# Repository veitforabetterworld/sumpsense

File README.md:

# SumpSense

Kapazitive Füllstandssensoren für **14,5-mm-Rohr** (schmaler Stab, 5-mm-Raster). Inspiriert vom [Seeed Grove Water Level Sensor](https://wiki.seeedstudio.com/Grove-Water-Level-Sensor/).

| Platine | Stufen | Bus | Doku |
|---------|--------|-----|------|
| [SumpSense-24i](hardware/sumpsense-24i/README.md) | 24 | I²C | Bestellen → [`firmware`](firmware/README.md#sumpsense-24i) |
| [SumpSense-16z](hardware/sumpsense-16z/README.md) | 16 | Zigbee 3.0 + Ventil | Bestellen → [`firmware`](firmware/README.md#sumpsense-16z) |
| [SumpSense-16z-v2](hardware/sumpsense-16z-v2/README.md) | 16 | Zigbee 3.0 + Ventil, ESP32-H2-MINI-1, 100,0 mm (+ 5,4 mm Antenne) | Bestellen → [`firmware`](firmware/README.md#sumpsense-16z) (`SS_BOARD=2`) |

Gerber/BOM je Board: `hardware/<name>/jlcpcb/` — erzeugen mit `python3 hardware/jlcpcb.py <name>`.

## Boardprüfung

`python3 hardware/check_boards.py [<name>]` führt DRC (mit Schaltplan-Parität) und ERC aus und meldet jeden Fehler und jede Warnung. Erlaubte Ausnahmen stehen in den Projektdateien, damit KiCad und das Skript dasselbe melden:

- `<name>.kicad_dru`: Der Schraubenkopf MH1 darf die Courtyards anderer Bauteile überdecken (einzige Ausnahme).
- `sumpsense-24i.kicad_pro`: In der ERC-Pin-Matrix ist „Bidirektional ↔ Power-Ausgang“ erlaubt, weil PA3 als Adressmerkmal fest an GND/VCC liegt.

Angepasste Footprints liegen in den Projektbibliotheken (`zig:`, `ssi:`), damit es keine Abweichungen von der KiCad-Bibliothek gibt.

Der Git-Hook `.githooks/pre-commit` startet die Prüfung bei jedem Commit, der Platinendateien enthält, und bricht den Commit bei Befunden ab. Einmal pro Klon aktivieren:

```bash
git config core.hooksPath .githooks
```

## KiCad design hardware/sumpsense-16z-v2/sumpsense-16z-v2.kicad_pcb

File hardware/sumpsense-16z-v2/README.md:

# SumpSense-16z-v2

Wie [SumpSense-16z](../sumpsense-16z/README.md), aber mit dem Modul **ESP32-H2-MINI-1-H4S** statt nacktem Chip: Quarz und Antenne sitzen im Modul, Quarz, Leiterantenne und Anpassnetz entfallen. Platine **14 × 100,0 mm**, die Modulantenne steht **5,4 mm** über (gesamt 105,4 mm; v1: 125 mm). Rohr **14,5 mm**, 16 Stufen à **5 mm**, Ausgang für **5-V-Magnetventil**.

## v1 oder v2?

| | v1 (`sumpsense-16z`) | v2 (`sumpsense-16z-v2`) |
|---|---|---|
| Funk | ESP32-H2FH4 + 32-MHz-Quarz + Leiterantenne DN007 | ESP32-H2-MINI-1-H4S (Quarz, Antenne, Funkzulassung im Modul) |
| Länge | 125 mm | 100,0 mm Platine + 5,4 mm Antenne = 105,4 mm |
| Bauhöhe Kopf | ca. 1,2 mm | **2,4 mm** (Modul) |
| LCSC-Lage | Chip „nicht für neue Designs“, Restbestand | Modul neu, Bestand schwankt |
| Teilepreis Funk (1 Stk.) | ≈ 2,19 $ | ≈ 3,77 $ |

Beide Platinen bleiben gepflegt: v1 fertigen, wenn das Modul nicht lieferbar ist.

## Platine bestellen (JLCPCB)

1. [`jlcpcb/`](jlcpcb/): Gerber-ZIP, BOM, CPL. Neu generieren: `python3 ../jlcpcb.py sumpsense-16z-v2`
2. **PCBA einseitig (oben):** Gerber, BOM und CPL hochladen. Die Lötpads auf der Unterseite (J1, J3, JP1) werden nicht bestückt.
3. **Antenne steht über die Platine:** So empfehlen es Espressif und JLCPCB selbst für Module mit Leiterantenne. JLCPCB bestückt nur mit Nutzenrand; der Rand darf nur an den Längsseiten liegen, am Antennenende muss frei bleiben. In der Bestellung als Bemerkung angeben: *„ESP32 module antenna overhangs the board edge on purpose, edge rails on the long sides only“*.
4. In der Bestückungsvorschau prüfen, dass die **Antenne des Moduls über das Platinenende** zeigt (CPL-Drehung des Moduls ist nicht gegen eine echte Bestellung geprüft).

## Anschluss

| Wo | Funktion |
|----|----------|
Alle Anschlüsse sind Lötpads (1,1 × 2,2 mm, Raster 1,425 mm) auf der **Unterseite unter dem Modul**:

| Wo | Pads | Funktion |
|----|------|----------|
| Unterkante | **PAIR** (JP1), **GND**, **5V**, **VLV** (J1) | Versorgung; Magnetventil zwischen **5V** und **VLV**. PAIR = GPIO9, mit dem GND-Pad daneben brücken: Pairing, Werksreset, Download-Modus |
| Oberkante | **D−**, **D+** (J3) | USB nur zum Flashen, dazu GND und 5V von der Unterkante |

Drähte von den Pads weg nach hinten oder zur Seite führen, nicht unter der überstehenden Antenne entlang.

## Aufbau

- **Modul am Platinenende**, nur der Antennenteil (5,4 mm) steht über; die Platinenkante liegt auf der Antennengrenze, 0,3 mm vor den äußeren GND-Pads.
- **Vias unter dem Modul:** Seitenpins und Endreihe gehen direkt unter dem Modul auf die Unterseite. Dadurch beginnen die Bauteile direkt hinter dem Modul.
- **Bauteile hinter dem Modul, dicht gepackt:** Pull-ups R18/R17 und C6 in einer Spalte am Modul, C3 und C4 untereinander daneben, rechts Regler U2, Freilaufdiode D1 senkrecht, R23 und Ventiltreiber Q1; R19 quer unter C4.
- **Alle 16 Sense-Leitungen auf der Unterseite**, kreuzungsfrei; vor der Widerstandsbank gehen sie über Vias nach oben.
- **Widerstandsbank direkt vor MAX:** Die MAX-Linie liegt gleich hinter der Bank in der Lücke vor E1; der Fächer zu den Elektroden knickt direkt hinter der Bank ab und reicht über MAX hinaus. Der Schraubenkopf MH1 (Ø 6 mm) ragt etwa 0,5 mm über die MAX-Linie.
- **GND-Fläche auf Ober- und Unterseite**, freie Flächen im Kopf über GND-Vias verbunden.
- **Vias 0,45/0,2 mm** (JLCPCB-Standard ohne Aufpreis).
- **Bahnbreiten:** Sense 0,2 mm, 3V3 0,3 mm (0,4 mm auf der Unterseite), GND 0,2–0,4 mm je nach Platz, 5V und Ventil 0,5 mm, Elektroden 0,25 mm.
- **Bestückungsdruck nur auf der Unterseite:** MAX-Linie, Eintauchtiefen (in den Lücken vor den Elektroden), Padbeschriftung und Platinenname. Die Gerber-Daten enthalten keinen Druck für die Oberseite (`../jlcpcb.py`).
- **GPIO-Zuordnung** folgt der Modul-Pinreihe (E01…E16 = GPIO 10, 11, 8, 9, 22, 25, 23, 24, 5, 4, 12, 14, 13, 1, 3, 2). Die Firmware braucht dafür `SS_BOARD=2`.
- **EN** mit 10 kΩ / 1 µF (R19, C6) nach Datenblatt; **VBAT** bleibt offen (im Modul an 3V3).
- Pull-ups **R17/R18 (1 MΩ)** an GPIO8/9 wie bei v1 (Messverfahren und Strapping).
- Der Schaltplan wird mit `python3 gen_sch.py` aus der Platine erzeugt.

## Firmware, Pairing, Smart Home

**[Firmware-README](../../firmware/README.md#sumpsense-16z)**: Bauen mit `SS_BOARD=2`, Flashen, PAIR-Tabelle, Home Assistant. Zigbee-Modell und Zigbee2MQTT-Konverter sind dieselben wie bei v1; OTA-Images haben einen eigenen Image-Typ (0x1012), damit v1- und v2-Images nicht vertauscht werden.

## Ungeprüft

- Kein Musteraufbau: Antennenleistung im Rohr, Kapazitätsmessung und Einschaltverhalten (EN-RC) sind nur nach Datenblatt ausgelegt.
- Überstehende Antenne bei JLCPCB nicht mit einer echten Bestellung geprüft (Nutzenrand siehe oben).
- Das Landmuster des Moduls ist nach Espressifs KiCad-Bibliothek nachgebaut; das 3D-Modell ist vereinfacht.

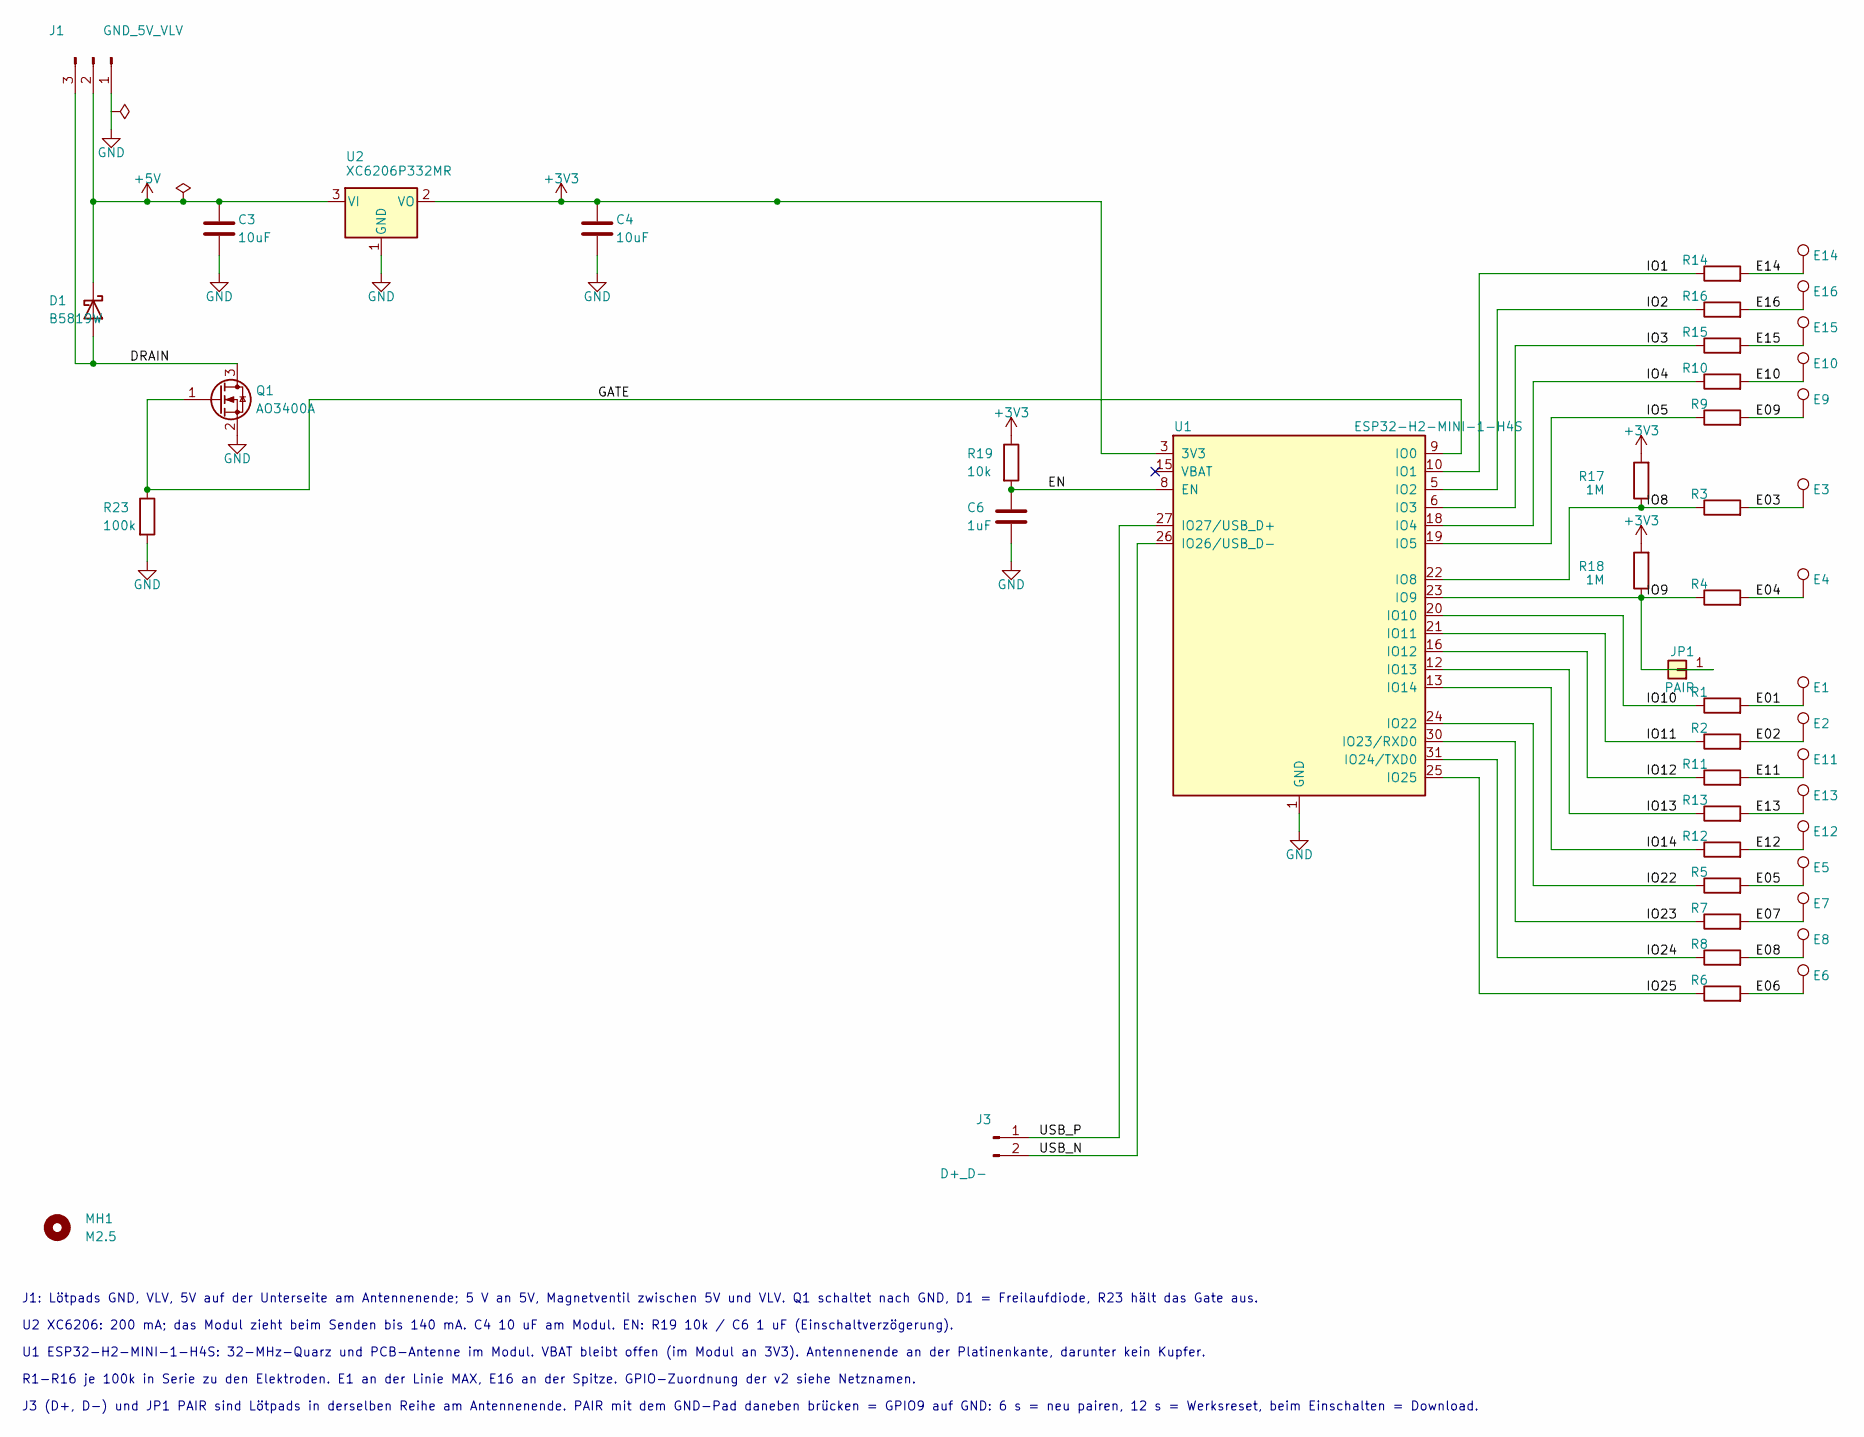
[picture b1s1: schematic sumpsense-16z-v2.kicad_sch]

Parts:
C3, C4: 10uF; C_0603_1608Metric
C6: 1uF; C_0402_1005Metric
D1: B5819W; D_SOD-123
E1: E01; electrode
E2: E02; electrode
E3: E03; electrode
E4: E04; electrode
E5: E05; electrode
E6: E06; electrode
E7: E07; electrode
E8: E08; electrode
E9: E09; electrode
E10: E10; electrode
E11: E11; electrode
E12: E12; electrode
E13: E13; electrode
E14: E14; electrode
E15: E15; electrode
E16: E16; electrode
J1: GND_5V_VLV; solder_pads_1x3
J3: D+_D-; solder_pads_1x2
JP1: PAIR; solder_pad
MH1: M2.5; MountingHole_2.7mm_M2.5
Q1: AO3400A; SOT-23
R1, R2, R3, R4, R5, R6, R7, R8, R9, R10, R11, R12, R13, R14, R15, R16, R23: 100k; R_0402_1005Metric
R17, R18: 1M; R_0402_1005Metric
R19: 10k; R_0402_1005Metric
U1: ESP32-H2-MINI-1-H4S; ESP32-H2-MINI-1
U2: XC6206P332MR; SOT-23-3

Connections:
+3V3: C4.1, R17.2, R18.2, R19.1, U1.3 (3V3), U2.2 (VO)
+5V: C3.1, D1.1 (K), J1.2, U2.3 (VI)
/DRAIN: D1.2 (A), J1.3, Q1.3 (D)
/E01: E1.1, R1.2
/E02: E2.1, R2.2
/E03: E3.1, R3.2
/E04: E4.1, R4.2
/E05: E5.1, R5.2
/E06: E6.1, R6.2
/E07: E7.1, R7.2
/E08: E8.1, R8.2
/E09: E9.1, R9.2
/E10: E10.1, R10.2
/E11: E11.1, R11.2
/E12: E12.1, R12.2
/E13: E13.1, R13.2
/E14: E14.1, R14.2
/E15: E15.1, R15.2
/E16: E16.1, R16.2
/EN: C6.1, R19.2, U1.8 (EN)
/GATE: Q1.1 (G), R23.1, U1.9 (IO0)
/IO1: R14.1, U1.10 (IO1)
/IO2: R16.1, U1.5 (IO2)
/IO3: R15.1, U1.6 (IO3)
/IO4: R10.1, U1.18 (IO4)
/IO5: R9.1, U1.19 (IO5)
/IO8: R3.1, R17.1, U1.22 (IO8)
/IO9: JP1.1, R4.1, R18.1, U1.23 (IO9)
/IO10: R1.1, U1.20 (IO10)
/IO11: R2.1, U1.21 (IO11)
/IO12: R11.1, U1.16 (IO12)
/IO13: R13.1, U1.12 (IO13)
/IO14: R12.1, U1.13 (IO14)
/IO22: R5.1, U1.24 (IO22)
/IO23: R7.1, U1.30 (IO23/RXD0)
/IO24: R8.1, U1.31 (IO24/TXD0)
/IO25: R6.1, U1.25 (IO25)
/USB_N: J3.2, U1.26 (IO26/USB_D-)
/USB_P: J3.1, U1.27 (IO27/USB_D+)
GND: C3.2, C4.2, C6.2, J1.1, Q1.2 (S), R23.2, U1.1 (GND), U1.2 (GND), U1.11 (GND), U1.14 (GND), U1.36 (GND), U1.37 (GND), U1.38 (GND), U1.39 (GND), U1.40 (GND), U1.41 (GND), U1.42 (GND), U1.43 (GND), U1.44 (GND), U1.45 (GND), U1.46 (GND), U1.47 (GND), U1.48 (GND), U1.49 (GND), U1.50 (GND), U1.51 (GND), U1.52 (GND), U1.53 (GND), U2.1 (GND)

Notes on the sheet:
J1: Lötpads GND, VLV, 5V auf der Unterseite am Antennenende; 5 V an 5V, Magnetventil zwischen 5V und VLV. Q1 schaltet nach GND, D1 = Freilaufdiode, R23 hält das Gate aus.
U2 XC6206: 200 mA; das Modul zieht beim Senden bis 140 mA. C4 10 uF am Modul. EN: R19 10k / C6 1 uF (Einschaltverzögerung).
U1 ESP32-H2-MINI-1-H4S: 32-MHz-Quarz und PCB-Antenne im Modul. VBAT bleibt offen (im Modul an 3V3). Antennenende an der Platinenkante, darunter kein Kupfer.
R1-R16 je 100k in Serie zu den Elektroden. E1 an der Linie MAX, E16 an der Spitze. GPIO-Zuordnung der v2 siehe Netznamen.
J3 (D+, D-) und JP1 PAIR sind Lötpads in derselben Reihe am Antennenende. PAIR mit dem GND-Pad daneben brücken = GPIO9 auf GND: 6 s = neu pairen, 12 s = Werksreset, beim Einschalten = Download.

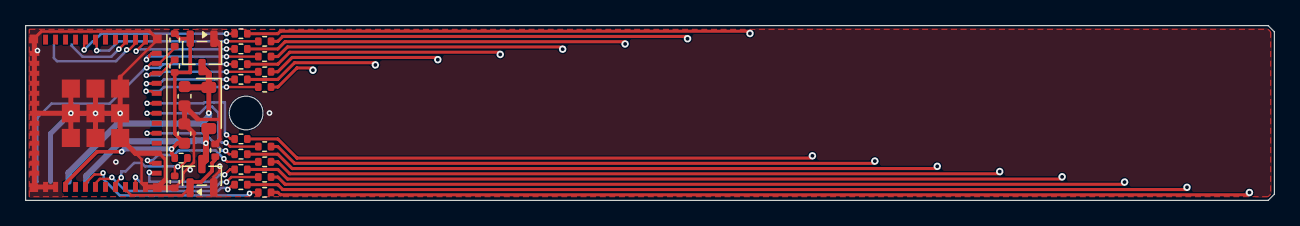
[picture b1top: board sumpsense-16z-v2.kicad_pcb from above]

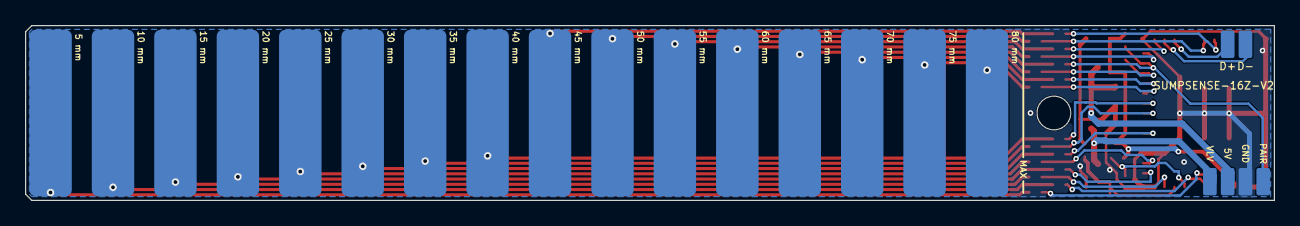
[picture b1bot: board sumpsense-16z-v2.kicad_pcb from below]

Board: 2 copper layers, 100.0 x 14.0 mm, 47 parts (19 on the bottom side), 40 nets.

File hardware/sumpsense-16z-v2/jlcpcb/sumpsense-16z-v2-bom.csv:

Comment,Designator,Footprint,LCSC Part #
10uF,"C3,C4",C_0603_1608Metric,C19702
1uF,C6,C_0402_1005Metric,C52923
B5819W,D1,D_SOD-123,C8598
AO3400A,Q1,SOT-23,C20917
100k,"R1,R2,R3,R4,R5,R6,R7,R8,R9,R10,R11,R12,R13,R14,R15,R16,R23",R_0402_1005Metric,C25741
1M,"R17,R18",R_0402_1005Metric,C26083
10k,R19,R_0402_1005Metric,C25744
ESP32-H2-MINI-1-H4S,U1,ESP32-H2-MINI-1,C47967030
XC6206P332MR,U2,SOT-23-3,C5446

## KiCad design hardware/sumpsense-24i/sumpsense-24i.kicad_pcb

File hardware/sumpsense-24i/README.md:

# SumpSense-24i

24 kapazitive Stufen, **2× ATtiny1616**, **I²C** (Seeed-kompatibel **0x78** / **0x77**). **14 × 141 mm**, Rohr **14,5 mm**, Stufen **5 mm** (120 mm Messbereich).

## Platine bestellen (JLCPCB)

1. [`jlcpcb/`](jlcpcb/): Gerber-ZIP, BOM, CPL.
2. Neu generieren: `python3 ../jlcpcb.py sumpsense-24i`
3. **PCBA:** Gerber, BOM und CPL zusammen hochladen.

## Anschluss

**J1** (2,54 mm): GND, VCC (3,3–5 V), SCL, SDA, UPDI U1, UPDI U2. Pull-ups auf der Platine. Füllstand: nasse Stufen am Stück ab **0x77** Byte 0, dann **0x78** Byte 0, × 5 mm.

## Firmware & Nutzen

Bauen, Flashen (UPDI U1 + U2), I²C-Nutzung: **[Firmware-README](../../firmware/README.md#sumpsense-24i)**.

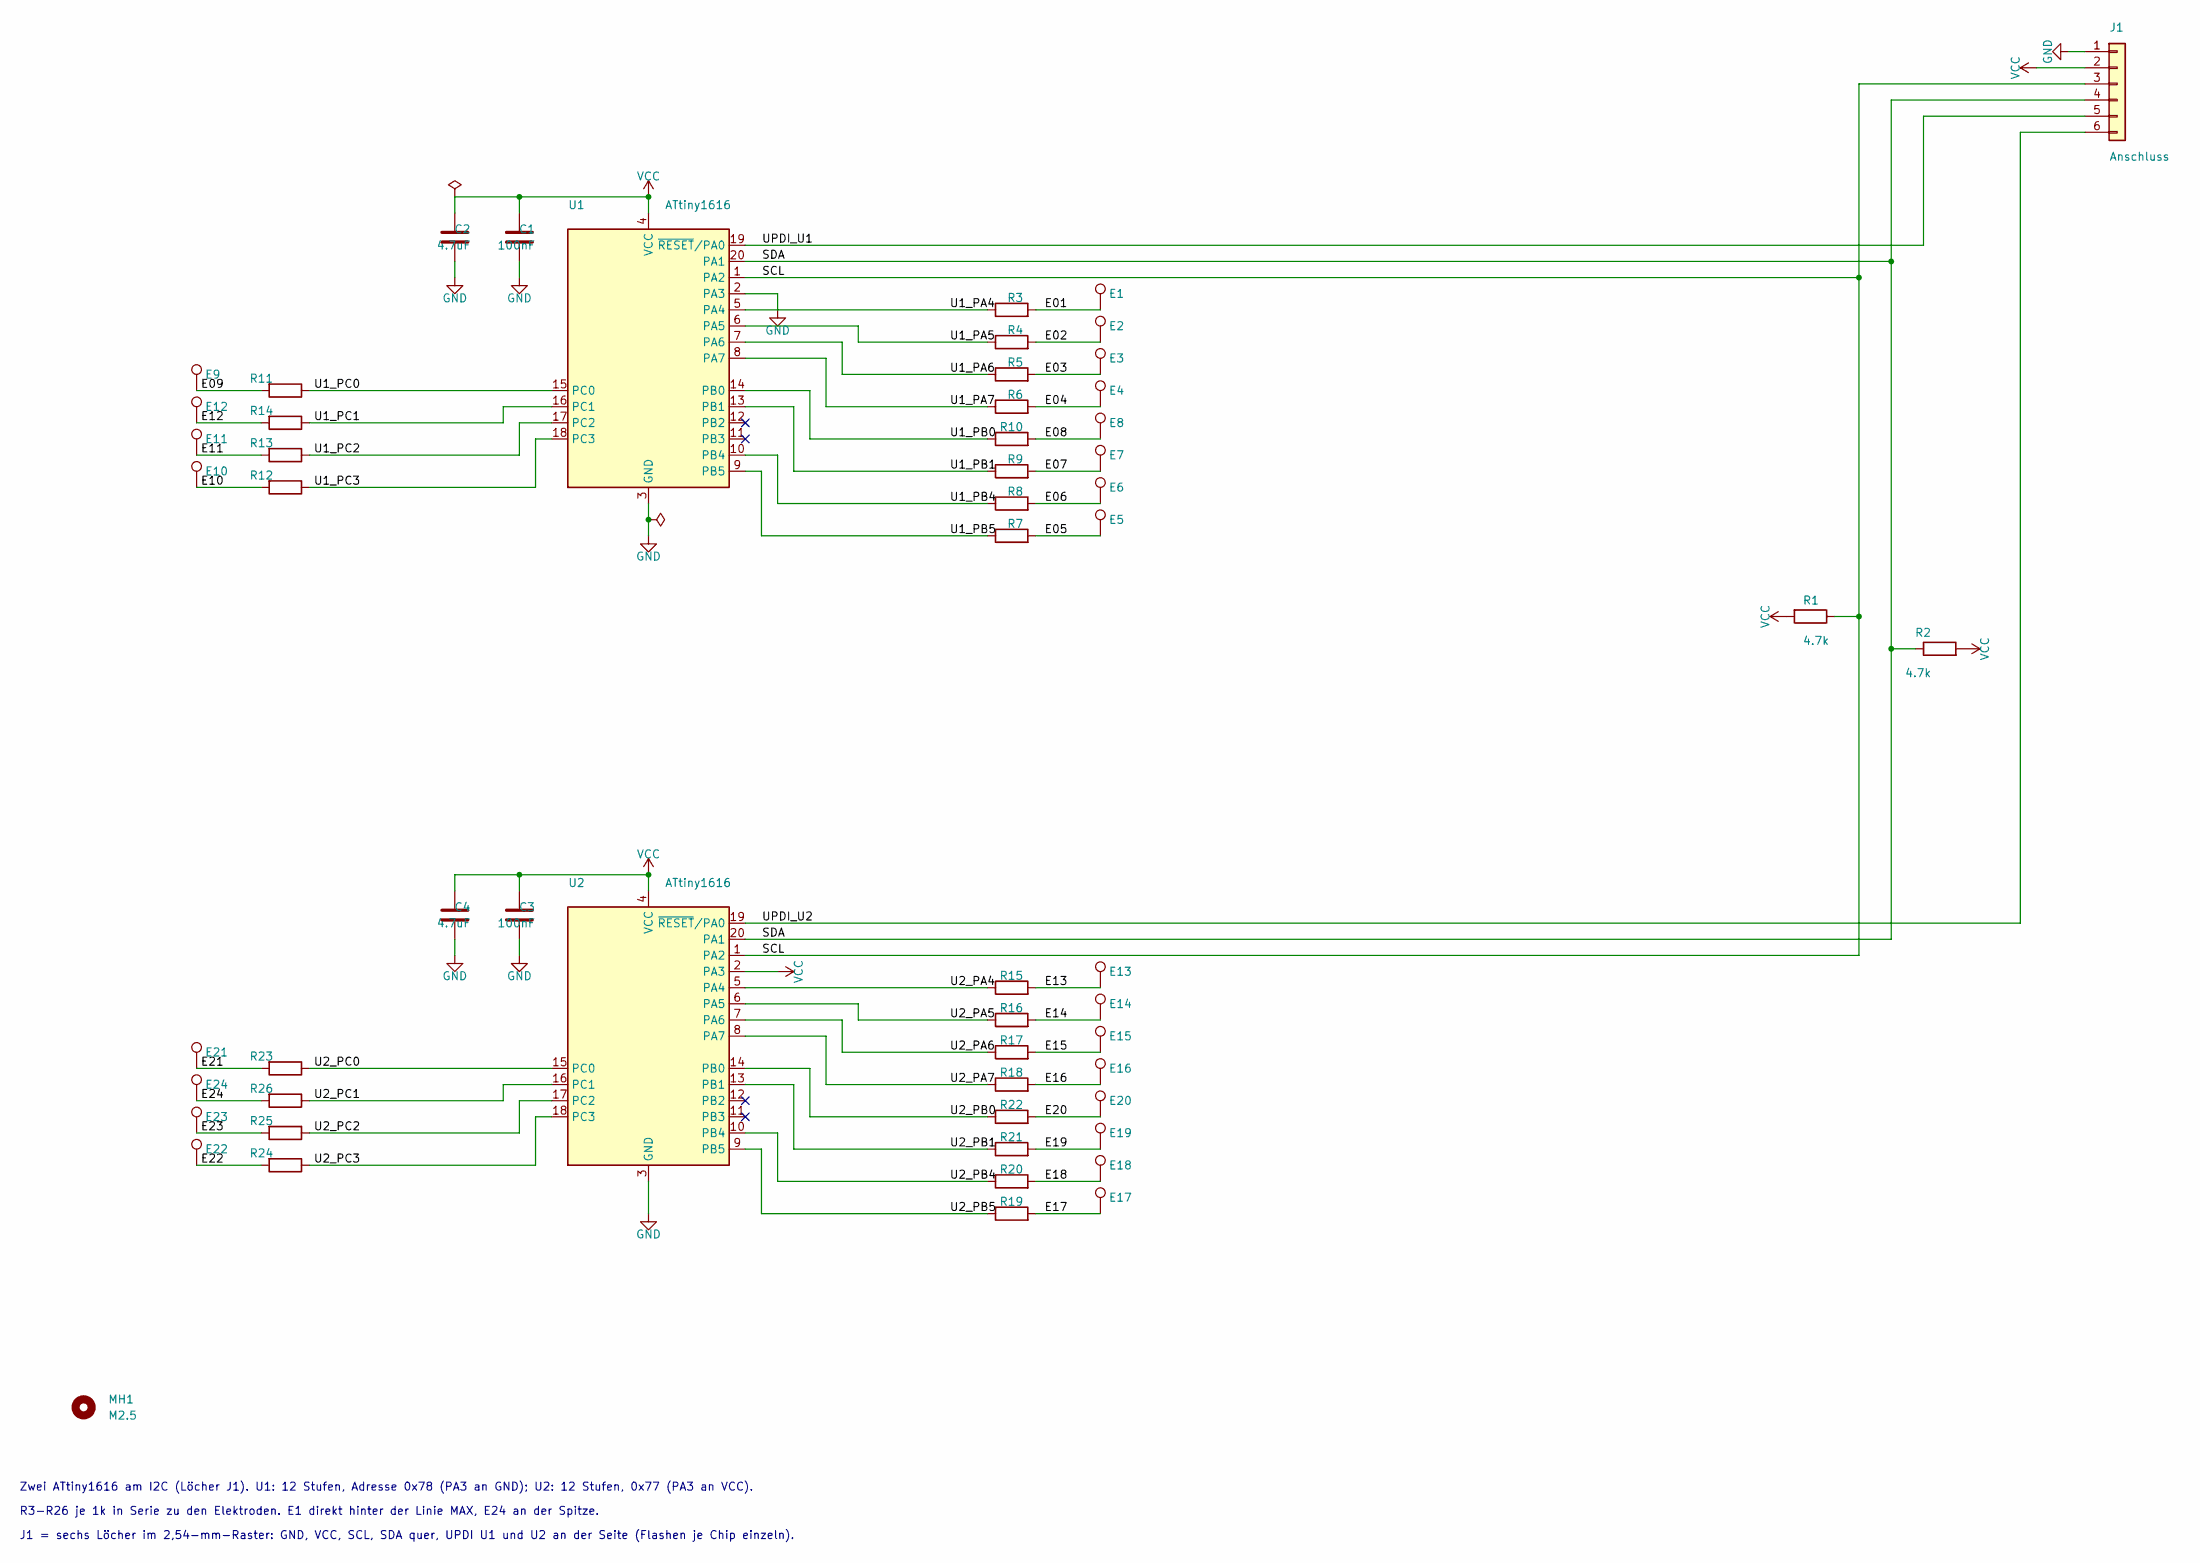
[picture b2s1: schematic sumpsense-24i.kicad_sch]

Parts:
C1, C3: 100nF; C_0402_1005Metric
C2, C4: 4.7uF; C_0402_1005Metric
E1: E01; electrode
E2: E02; electrode
E3: E03; electrode
E4: E04; electrode
E5: E05; electrode
E6: E06; electrode
E7: E07; electrode
E8: E08; electrode
E9: E09; electrode
E10: E10; electrode
E11: E11; electrode
E12: E12; electrode
E13: E13; electrode
E14: E14; electrode
E15: E15; electrode
E16: E16; electrode
E17: E17; electrode
E18: E18; electrode
E19: E19; electrode
E20: E20; electrode
E21: E21; electrode
E22: E22; electrode
E23: E23; electrode
E24: E24; electrode
J1: Anschluss; holes_6
MH1: M2.5; MountingHole_2.7mm_M2.5
R1, R2: 4.7k; R_0402_1005Metric
R3, R4, R5, R6, R7, R8, R9, R10, R11, R12, R13, R14, R15, R16, R17, R18, R19, R20, R21, R22, R23, R24, R25, R26: 1k; R_0402_1005Metric
U1, U2: ATtiny1616; VQFN-20-1EP_3x3mm_P0.4mm_EP1.7x1.7mm

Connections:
/E01: E1.1, R3.2
/E02: E2.1, R4.2
/E03: E3.1, R5.2
/E04: E4.1, R6.2
/E05: E5.1, R7.2
/E06: E6.1, R8.2
/E07: E7.1, R9.2
/E08: E8.1, R10.2
/E09: E9.1, R11.2
/E10: E10.1, R12.2
/E11: E11.1, R13.2
/E12: E12.1, R14.2
/E13: E13.1, R15.2
/E14: E14.1, R16.2
/E15: E15.1, R17.2
/E16: E16.1, R18.2
/E17: E17.1, R19.2
/E18: E18.1, R20.2
/E19: E19.1, R21.2
/E20: E20.1, R22.2
/E21: E21.1, R23.2
/E22: E22.1, R24.2
/E23: E23.1, R25.2
/E24: E24.1, R26.2
/SCL: J1.3, R1.1, U1.1 (PA2), U2.1 (PA2)
/SDA: J1.4, R2.1, U1.20 (PA1), U2.20 (PA1)
/U1_PA5: R4.1, U1.6 (PA5)
/U1_PA6: R5.1, U1.7 (PA6)
/U1_PA7: R6.1, U1.8 (PA7)
/U1_PB0: R10.1, U1.14 (PB0)
/U1_PB1: R9.1, U1.13 (PB1)
/U1_PB4: R8.1, U1.10 (PB4)
/U1_PB5: R7.1, U1.9 (PB5)
/U1_PC0: R11.1, U1.15 (PC0)
/U1_PC1: R14.1, U1.16 (PC1)
/U1_PC2: R13.1, U1.17 (PC2)
/U1_PC3: R12.1, U1.18 (PC3)
/U2_PA4: R15.1, U2.5 (PA4)
/U2_PA5: R16.1, U2.6 (PA5)
/U2_PA6: R17.1, U2.7 (PA6)
/U2_PA7: R18.1, U2.8 (PA7)
/U2_PB0: R22.1, U2.14 (PB0)
/U2_PB1: R21.1, U2.13 (PB1)
/U2_PB4: R20.1, U2.10 (PB4)
/U2_PB5: R19.1, U2.9 (PB5)
/U2_PC0: R23.1, U2.15 (PC0)
/U2_PC1: R26.1, U2.16 (PC1)
/U2_PC2: R25.1, U2.17 (PC2)
/U2_PC3: R24.1, U2.18 (PC3)
/UPDI_U1: J1.5, U1.19 (~RESET/PA0)
/UPDI_U2: J1.6, U2.19 (~RESET/PA0)
VCC: C1.2, C2.2, C3.2, C4.2, J1.2, R1.2, R2.2, U1.4 (VCC), U2.2 (PA3), U2.4 (VCC)

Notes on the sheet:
Zwei ATtiny1616 am I2C (Löcher J1). U1: 12 Stufen, Adresse 0x78 (PA3 an GND); U2: 12 Stufen, 0x77 (PA3 an VCC).
R3-R26 je 1k in Serie zu den Elektroden. E1 direkt hinter der Linie MAX, E24 an der Spitze.
J1 = sechs Löcher im 2,54-mm-Raster: GND, VCC, SCL, SDA quer, UPDI U1 und U2 an der Seite (Flashen je Chip einzeln).

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
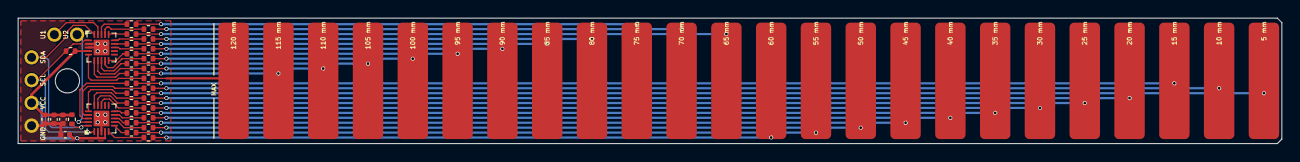
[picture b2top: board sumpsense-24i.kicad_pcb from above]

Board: 2 copper layers, 141.1 x 14.0 mm, 58 parts (0 on the bottom side), 54 nets.

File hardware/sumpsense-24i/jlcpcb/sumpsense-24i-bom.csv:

Comment,Designator,Footprint,LCSC Part #
100nF,"C1,C3",C_0402_1005Metric,C1525
4.7uF,"C2,C4",C_0402_1005Metric,C23733
4.7k,"R1,R2",R_0402_1005Metric,C25900
1k,"R3,R4,R5,R6,R7,R8,R9,R10,R11,R12,R13,R14,R15,R16,R17,R18,R19,R20,R21,R22,R23,R24,R25,R26",R_0402_1005Metric,C11702
ATtiny1616,"U1,U2",VQFN-20-1EP_3x3mm_P0.4mm_EP1.7x1.7mm,C507118

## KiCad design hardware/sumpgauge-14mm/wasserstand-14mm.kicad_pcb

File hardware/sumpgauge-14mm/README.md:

# Wasserstand 14 mm

Kapazitiver Füllstandssensor für **14,5-mm-Rohr** (Platine **14,0 × 138,0 mm**). Schaltung wie der [Seeed Grove Water Level Sensor (10 cm)](https://wiki.seeedstudio.com/Grove-Water-Level-Sensor/). Zwei **ATtiny1616**, **I2C** am Grove. **U1** = **12** Segmente am Stecker (**0x78**), **U2** = **8** Segmente an der Spitze (**0x77**). Segmentabstand **5 mm**. Linie **MAX**: nicht tiefer eintauchen.

## Anschluss im Betrieb

Grove-Kabel an **J1** (trockenes Ende). Elektroden zur Spitze.

| Grove | Signal |
|-------|--------|
| Gelb | SCL |
| Weiß | SDA |
| Rot | VCC (3,3 V oder 5 V) |
| Schwarz | GND |

Master liest **0x78**, dann **0x77** (Beispiel: [`examples/water-level-sensor-demo.ino`](../../examples/water-level-sensor-demo.ino)).

## Flashen (Adafruit UPDI Friend)

Vier Löcher **J3** unter dem Grove (Dupont nur beim Flashen). Von der Stecker-Kante: **GND · VCC · U1 · U2** — schwarz / rot / weiß an Friend; weiß nacheinander auf **U1**, dann **U2**. Nur ein Chip, Grove ab, eine Spannungsquelle.

```bash
cd ../../firmware
UPDI_PORT=/dev/ttyACM0 ./flash.sh u1
UPDI_PORT=/dev/ttyACM0 ./flash.sh u2
```

Details, Firmware-Quellen, Dump vom Original-Sensor: [`../../firmware/README.md`](../../firmware/README.md).

**Firmware:** Seeed veröffentlicht die **MCU-Firmware nicht** (nur Hardware + Arduino-Demo). Für **100 % Seeed-I2C** zuerst mit `dump.sh` von einem Original-Grove lesen. Ohne `U1.hex`/`U2.hex` nutzt `flash.sh` Community-HEX (`community/`) — funktioniert, aber **anderes I2C-Protokoll** (16-Bit je Pad).

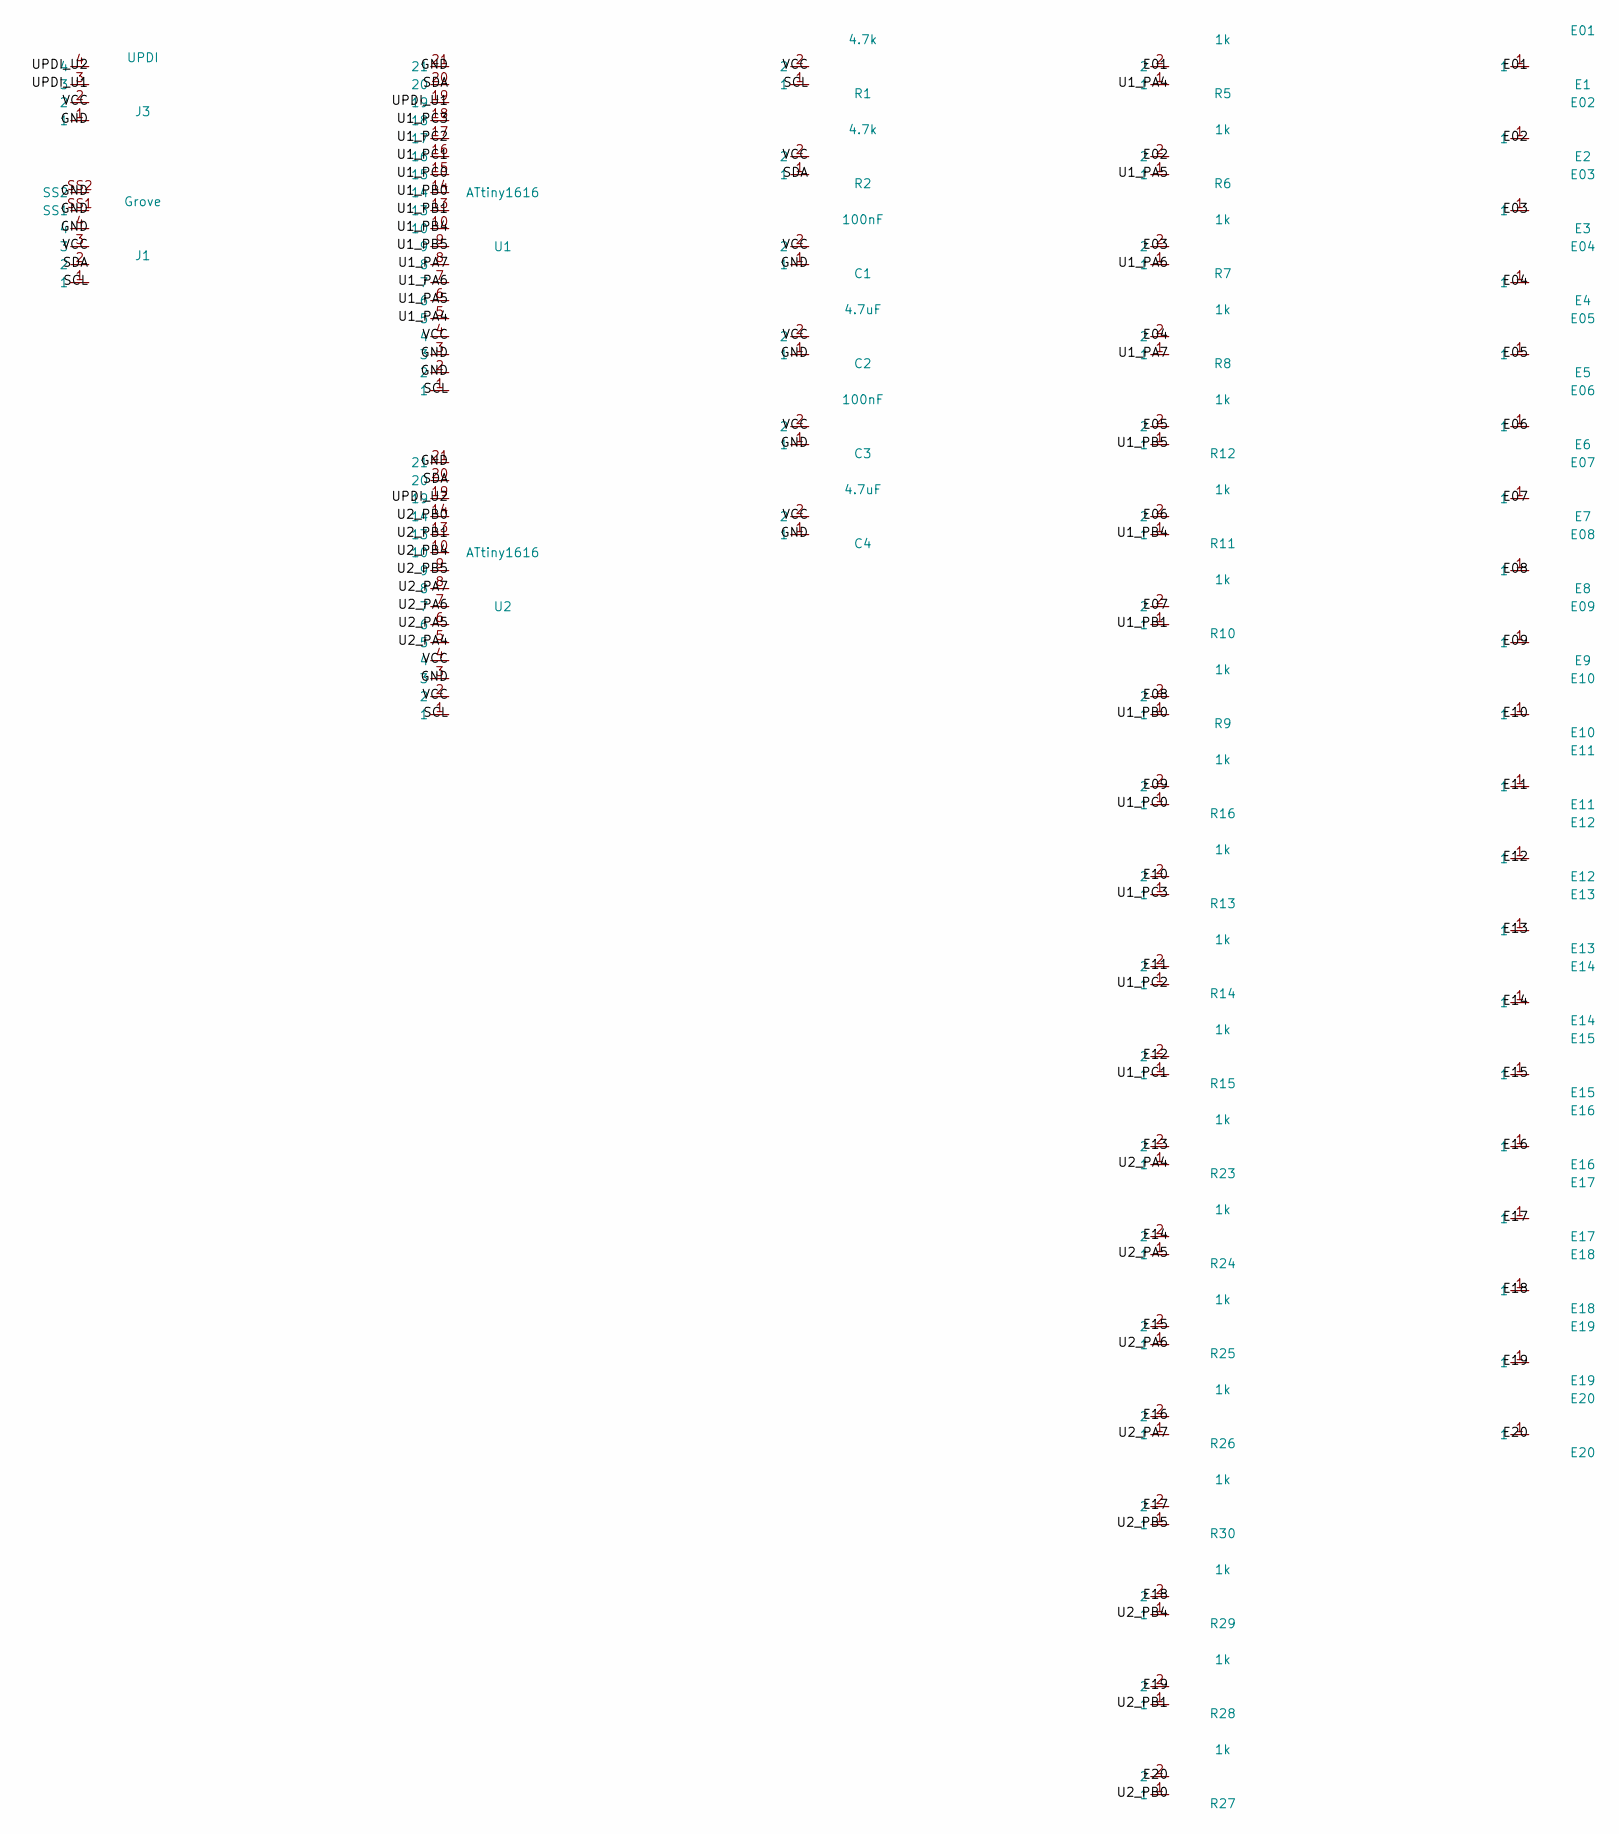
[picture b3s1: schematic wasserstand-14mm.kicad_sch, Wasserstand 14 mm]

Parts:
C1, C3: 100nF
C2, C4: 4.7uF
E1: E01
E2: E02
E3: E03
E4: E04
E5: E05
E6: E06
E7: E07
E8: E08
E9: E09
E10: E10
E11: E11
E12: E12
E13: E13
E14: E14
E15: E15
E16: E16
E17: E17
E18: E18
E19: E19
E20: E20
J1: Grove
J3: UPDI
R1, R2: 4.7k
R5, R6, R7, R8, R9, R10, R11, R12, R13, R14, R15, R16, R23, R24, R25, R26, R27, R28, R29, R30: 1k
U1, U2: ATtiny1616

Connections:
E01: E1.1, R5.2
E02: E2.1, R6.2
E03: E3.1, R7.2
E04: E4.1, R8.2
E05: E5.1, R12.2
E06: E6.1, R11.2
E07: E7.1, R10.2
E08: E8.1, R9.2
E09: E9.1, R16.2
E10: E10.1, R13.2
E11: E11.1, R14.2
E12: E12.1, R15.2
E13: E13.1, R23.2
E14: E14.1, R24.2
E15: E15.1, R25.2
E16: E16.1, R26.2
E17: E17.1, R30.2
E18: E18.1, R29.2
E19: E19.1, R28.2
E20: E20.1, R27.2
GND: C1.1, C2.1, C3.1, C4.1, J1.4, J1.SS1, J1.SS2, J3.1, U1.2, U1.3, U1.21, U2.3, U2.21
SCL: J1.1, R1.1, U1.1, U2.1
SDA: J1.2, R2.1, U1.20, U2.20
U1_PA4: R5.1, U1.5
U1_PA5: R6.1, U1.6
U1_PA6: R7.1, U1.7
U1_PA7: R8.1, U1.8
U1_PB0: R9.1, U1.14
U1_PB1: R10.1, U1.13
U1_PB4: R11.1, U1.10
U1_PB5: R12.1, U1.9
U1_PC0: R16.1, U1.15
U1_PC1: R15.1, U1.16
U1_PC2: R14.1, U1.17
U1_PC3: R13.1, U1.18
U2_PA4: R23.1, U2.5
U2_PA5: R24.1, U2.6
U2_PA6: R25.1, U2.7
U2_PA7: R26.1, U2.8
U2_PB0: R27.1, U2.14
U2_PB1: R28.1, U2.13
U2_PB4: R29.1, U2.10
U2_PB5: R30.1, U2.9
UPDI_U1: J3.3, U1.19
UPDI_U2: J3.4, U2.19
VCC: C1.2, C2.2, C3.2, C4.2, J1.3, J3.2, R1.2, R2.2, U1.4, U2.2, U2.4

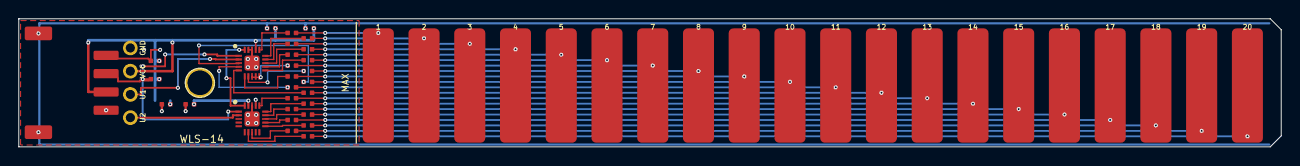
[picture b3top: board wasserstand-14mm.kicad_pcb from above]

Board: 2 copper layers, 138.0 x 14.0 mm, 51 parts (0 on the bottom side), 46 nets.

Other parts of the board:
MH1: M2.5; mount

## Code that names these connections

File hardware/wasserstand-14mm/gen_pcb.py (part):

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    u1 = _pad_xy(pads, "U1", "4")
    u2 = _pad_xy(pads, "U2", "4")
    hv = _pad_xy(pads, "J3", "2")
    pa3 = _pad_xy(pads, "U2", "2")
    bus_y = 2.35
    riser_x = 15.6 + D.HEAD
    w = 0.30
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        tap(via_xy)
        trunk(via_xy, (via_xy[0], join_y))
    trunk((u2[0], D.VCC_U2_BUS_Y), (riser_x, D.VCC_U2_BUS_Y))
    # U2 PA3 = VCC, Adress-Strap. Neben dem VDD-Hals, nicht durch Pin 1.
    _seg(tracks, pa3, (pa3[0], D.VCC_U2_BUS_Y), 0.18, "VCC")
    tap((pa3[0], D.VCC_U2_BUS_Y))
    trunk((pa3[0], D.VCC_U2_BUS_Y), (u2[0], D.VCC_U2_BUS_Y))


def connect_mcu_io(pads, vias, tracks):
    """PA1/PA2 direkt auf SDA/SCL. PA0 jeweils an das eigene Loch. Kein Jumper."""
    r1 = _pad_xy(pads, "R1", "1")
    r2 = _pad_xy(pads, "R2", "1")
    u1_scl = _pad_xy(pads, "U1", "1")
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    _seg(tracks, scl_cross, scl_up, 0.2, "SCL")
    _seg(tracks, scl_up, (r1[0], u1_scl[1]), 0.2, "SCL")
    _seg(tracks, (r1[0], u1_scl[1]), r1, 0.2, "SCL")
    # U2 auf demselben Riegel. Senkrecht an PC1 vorbei, Via erst darunter.
    dx, dx2 = 23.85 + H, 23.40 + H
    _seg(tracks, u2_scl, (dx, u2_scl[1]), 0.2, "SCL")
    _seg(tracks, (dx, u2_scl[1]), (dx, 6.50), 0.2, "SCL")
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    _seg(tracks, (dx2, 6.50), (dx2, u1_scl[1]), 0.2, "SCL", "B.Cu")
    _seg(tracks, (dx2, u1_scl[1]), scl_cross, 0.2, "SCL", "B.Cu")

    # SDA. PC3 fällt bei x=20,4+HEAD auf der Oberseite, der VCC-Steigleiter bei x=14,2+HEAD.
    x_bus = 13.55
    a, b, c = 22.4 + H, 21.0 + H, 16.7 + H
    _seg(tracks, u1_sda, (a, u1_sda[1]), 0.2, "SDA")
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    _seg(tracks, (sx, 11.00), (x_bus, 11.00), 0.2, "SDA", "B.Cu")
    _seg(tracks, (x_bus, 11.00), (x_bus, r2[1]), 0.2, "SDA", "B.Cu")

    # UPDI. Jedes PA0 an sein Loch unter dem Stecker.
    lane = 7.55
    _seg(tracks, u1_up, (22.2 + H, u1_up[1]), 0.2, "UPDI_U1")
    _seg(tracks, (22.2 + H, u1_up[1]), (22.2 + H, 4.40), 0.2, "UPDI_U1")
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

def is_sense(net):
    return net.startswith(("U1_", "U2_")) and not net.endswith(("PA0", "PA1", "PA2"))


def route_sense(pads, vias, tracks):
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        rx, ry = res_at[net]
        front(net, [(px, py), (jx, py), (jx, ry), (rx, ry)])

    # PA4 links neben der +x-Reihe, gerade auf die eigene Bahn.
    for net in ("U1_PA4", "U2_PA4"):
        px, py = pin_at[net]
        rx, ry = res_at[net]
        # 0,25 mm nach rechts, sonst klebt die Bahn an der VDD-Via.
        front(net, [(px, py), (px + 0.28, py), (px + 0.28, ry), (rx, ry)])

    # U1 rechte Flanke. PC1 liegt auf y=8,09. PC0 bleibt darunter.
    # PB0 steigt links von PB1 ab, beide Abstände an den EP-Vias vorbei.
    px, py = pin_at["U1_PC0"]
    rx, ry = res_at["U1_PC0"]
    front("U1_PC0", [(px, py), (px, 7.55), (29.00 + H, 7.55), (29.00 + H, ry), (rx, ry)])

    px, py = pin_at["U1_PB0"]
    rx, ry = res_at["U1_PB0"]
    front("U1_PB0", [(px, py), (px, 6.95), (27.90 + H, 6.95)])
    down("U1_PB0", (27.90 + H, 6.95))
    back("U1_PB0", [(27.90 + H, 6.95), (27.90 + H, ry), (rx, ry)])
    down("U1_PB0", (rx, ry))

    px, py = pin_at["U1_PB1"]
    rx, ry = res_at["U1_PB1"]
    front("U1_PB1", [(px, py), (px, 6.40), (27.15 + H, 6.40)])
    down("U1_PB1", (27.15 + H, 6.40))
    back("U1_PB1", [(27.15 + H, 6.40), (27.15 + H, ry), (rx, ry)])
    down("U1_PB1", (rx, ry))

    # U1 linke Flanke. PC1 oben herum. PC2 und PC3 auf der Unterseite, sonst kreuzen sie PC1.
    px, py = pin_at["U1_PC1"]
    rx, ry = res_at["U1_PC1"]
    front("U1_PC1", [(px, py), (24.20 + H, py), (24.20 + H, ry), (rx, ry)])

    px, py = pin_at["U1_PC2"]
    rx, ry = res_at["U1_PC2"]
    front("U1_PC2", [(px, py), (22.60 + H, py), (22.60 + H, 5.70)])
    down("U1_PC2", (22.60 + H, 5.70))
    back("U1_PC2", [(22.60 + H, 5.70), (22.60 + H, ry), (rx, ry)])
    down("U1_PC2", (rx, ry))

    px, py = pin_at["U1_PC3"]
    rx, ry = res_at["U1_PC3"]
    # Oberseite kreuzt SCL, Unterseite bleibt darunter und geht nach rechts, nicht durch den Steigleiter.
    front("U1_PC3", [(px, py), (px, 4.90), (20.40 + H, 4.90), (20.40 + H, 2.92)])
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    back("U1_PC3", [(20.40 + H, 2.92), (32.35 + H, 2.92), (32.35 + H, ry), (rx, ry)])
    down("U1_PC3", (rx, ry))

    # U2 rechte Flanke, beide Ziele neben dem Pin. PB1 zuerst runter, PB0 danach.
    px, py = pin_at["U2_PB1"]
    rx, ry = res_at["U2_PB1"]
    front("U2_PB1", [(px, py), (px, 13.05), (28.20 + H, 13.05), (28.20 + H, ry), (rx, ry)])
    px, py = pin_at["U2_PB0"]
    rx, ry = res_at["U2_PB0"]
    front("U2_PB0", [(px, py), (px, 13.40), (28.70 + H, 13.40), (28.70 + H, ry), (rx, ry)])

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            tracks.append(Track(x, y, x, y + 0.9, 0.22, "F.Cu", "GND"))
            continue
        if part.kind == "qfn" and pad.name == "2":
            # U1 PA3 an das benachbarte GND-Pad. Beide Netze sind GND.
            tracks.append(Track(x, y, x + 0.40, y, 0.18, "F.Cu", "GND"))
            continue
        if part.kind in ("c0402",):
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        )
    elif part.kind == "hdr":
        for pad in part.pads:
            label = {"GND": "GND", "VCC": "VCC", "UPDI_U1": "U1", "UPDI_U2": "U2"}[pad.net]
            lines.append(
                f'\t\t(fp_text user "{label}" (at 1.35 {pad.y:.2f} 270) (layer "F.SilkS") (uuid "{uid()}") '
                f'(effects (font (size 0.55 0.55) (thickness 0.08))))'
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    for part, pad, x, y in pads:
        if not pad.net or pad.net in D.elec_nets():
            continue
        # PA1/PA2 sind SCL/SDA, aber von Hand an den Pullup geführt.
        if pad.net in ("SCL", "SDA") and part.kind == "qfn":
            continue
        groups[pad.net].append((pad, x, y))
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        # Sense-Flucht vom QFN zuerst, sonst frisst VCC/I2C den Kanal unter den Chips.
        if n == "U1_PB0":
            return (0, 0)
        if n.endswith(("PA0", "PA1", "PA2")):
            return (1, 0)
        if n == "SDA":
            return (2, 5)
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
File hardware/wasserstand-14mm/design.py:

"""Kapazitiver Wasserstandsensor, 14 mm breit, für Rohr-Innendurchmesser 14,5 mm.

Einzige Quelle für Schaltung und Lage. Platine: python3 gen_pcb.py

Koordinaten: x = 0 am Stecker (trocken, oben), wächst zur Spitze (nass).
y = 0 .. BOARD_W quer zur Länge. Alle Bauteile auf der Oberseite.

Schaltung = Seeed Grove Water Level Sensor (10 cm), Eagle 9.2.2:
zwei ATtiny1616. Pin → Elektrode folgt der Originalplatine. Segmentabstand 5 mm.
PA3 von U1 liegt an GND, PA3 von U2 an VCC. Eine spätere Firmware kann daran
0x78 und 0x77 unterscheiden. Die Seeed-Werksfirmware liest PA3 nicht.

Querschnitt Rohr: Breite 14 mm ist eine Sehne in 14,5 mm. Bauteilseite zeigt
in den größeren Kreisabschnitt (siehe tube_clearance()).
"""

from dataclasses import dataclass, field

BOARD_W = 14.0
THICKNESS = 1.6
TUBE_ID = 14.5

N = 20
PITCH = 5.0
ELEC_ALONG = 3.4          # Elektrode in x (Original 3,0 mm bei 20 mm Breite)
ELEC_Y0 = 1.05
ELEC_Y1 = 13.55
LANE0 = 1.55              # y der untersten Sense-Bahn (E01)
LANE1 = 12.85

CLEARANCE = 0.15
TRACE = 0.20
VIA_SIZE = 0.45
VIA_DRILL = 0.20

# Elektronikblock 0,7 mm zum Stecker. Zusammen mit der wegfallenden Stirn: Länge 138 mm.
HEAD = -0.7
# Signalkontakte. Gehäuse und Öffnung liegen in -x, an der trockenen Kante.
CONN = (9.55, 7.0)
# 1×4 Durchkontaktierung unter dem Stecker, Raster 2,54 mm, Bohrung 1,0 mm.
HDR_X = 12.20
HDR_Y = 3.19              # Pin 1 = GND, dann VCC, U1, U2
U1_POS = (26.2 + HEAD, 4.85)
U2_POS = (26.2 + HEAD, 10.95)
RES_X_EVEN = 30.55 + HEAD
RES_X_ODD = 32.30 + HEAD
VIA_X = 34.20 + HEAD
ELEC0_X = 40.0 + HEAD

# Rohrclip: ein M2,5-Loch (y=7). Zweites Loch (Richtung U2) → Routing-Umbau. mount/clip.scad
MOUNT_Y = 7.0
MOUNT_X = 20.5 + HEAD
MOUNT_DRILL = 2.7
MOUNT_PAD = 3.2
# Router/Abstand: Bohrkante + Regelabstand + halbe Bahn (VCC-Stamm 0,30 mm).
MOUNT_BLOCK_R = MOUNT_DRILL / 2 + CLEARANCE + 0.30 / 2
# VCC-Querstrang zwischen den Chips, unterhalb MH1 mit Reserve.
VCC_U2_BUS_Y = MOUNT_Y + MOUNT_DRILL / 2 + 0.30 / 2 + 0.45
# Altname für Clip-Export
MOUNT_X1 = MOUNT_X


def lane_y(i: int) -> float:
    return LANE0 + i * (LANE1 - LANE0) / (N - 1)


def elec_x(i: int) -> float:
    return ELEC0_X + i * PITCH


def board_length() -> float:
    return elec_x(N - 1) + ELEC_ALONG / 2 + 2.0


def tube_clearance() -> tuple[float, float]:
    """Freie Höhe über/unter der Platinenoberfläche, Platine mittig auf der Sehne.

    Rückgabe: (große Seite, kleine Seite) in mm. Bauteile gehören auf die große Seite.
    """
    import math
    r = TUBE_ID / 2
    d = math.sqrt(r * r - (BOARD_W / 2) ** 2)
    half_t = THICKNESS / 2
    return (r + d - half_t, r - d - half_t)


# VQFN-20 3×3 mm, 0,4 mm Raster. Pin 1 = oben links der linken Flanke, gegen den Uhrzeigersinn
# (Draufsicht, +x zur Spitze, +y nach rechts). Entspricht Datasheet ATtiny1616 20-Pin VQFN.
PIN = {
    "PA2": 1, "PA3": 2, "GND": 3, "VDD": 4, "PA4": 5,
    "PA5": 6, "PA6": 7, "PA7": 8, "PB5": 9, "PB4": 10,
    "PB3": 11, "PB2": 12, "PB1": 13, "PB0": 14, "PC0": 15,
    "PC1": 16, "PC2": 17, "PC3": 18, "PA0": 19, "PA1": 20,
    "EP": 21,
}


def qfn_local(pin: int) -> tuple[float, float, float, float]:
    """(x, y, Breite, Höhe) relativ zur Chipmitte. Padmittelpunkt."""
    span = 1.45
    pw, pl = 0.22, 0.70
    xs = (-0.8, -0.4, 0.0, 0.4, 0.8)
    if 1 <= pin <= 5:
        return (xs[pin - 1], -span, pw, pl)
    if 6 <= pin <= 10:
        return (span, xs[pin - 6], pl, pw)
    if 11 <= pin <= 15:
        return (xs[4 - (pin - 11)], span, pw, pl)
    if 16 <= pin <= 20:
        return (-span, xs[4 - (pin - 16)], pl, pw)
    if pin == 21:
        return (0.0, 0.0, 1.65, 1.65)
    raise KeyError(pin)


# Elektrode 1 = am nächsten am Stecker (trocken), 20 = Spitze (zuerst nass).
# Widerstands-Refs wie auf der Seeed-Platine.
SENSORS = [
    (1, "U1", "PA4", "R5"),
    (2, "U1", "PA5", "R6"),
    (3, "U1", "PA6", "R7"),
    (4, "U1", "PA7", "R8"),
    (5, "U1", "PB5", "R12"),
    (6, "U1", "PB4", "R11"),
    (7, "U1", "PB1", "R10"),
    (8, "U1", "PB0", "R9"),
    (9, "U1", "PC0", "R16"),
    (10, "U1", "PC3", "R13"),
    (11, "U1", "PC2", "R14"),
    (12, "U1", "PC1", "R15"),
    (13, "U2", "PA4", "R23"),
    (14, "U2", "PA5", "R24"),
    (15, "U2", "PA6", "R25"),
    (16, "U2", "PA7", "R26"),
    (17, "U2", "PB5", "R30"),
    (18, "U2", "PB4", "R29"),
    (19, "U2", "PB1", "R28"),
    (20, "U2", "PB0", "R27"),
]


@dataclass
class Pad:
    name: str
    x: float
    y: float
    w: float
    h: float
    net: str
    mask: bool = True
    paste: bool = True


@dataclass
class Part:
    ref: str
    value: str
    kind: str
    x: float
    y: float
    pads: list = field(default_factory=list)


def _r(ref, value, x, y, n1, n2) -> Part:
    return Part(ref, value, "r0402", x, y, [
        Pad("1", -0.46, 0.0, 0.50, 0.50, n1),
        Pad("2", 0.46, 0.0, 0.50, 0.50, n2),
    ])


def _c(ref, value, x, y, n1, n2) -> Part:
    return Part(ref, value, "c0402", x, y, [
        Pad("1", -0.46, 0.0, 0.50, 0.50, n1),
        Pad("2", 0.46, 0.0, 0.50, 0.50, n2),
    ])


def _qfn(ref, x, y, nets: dict) -> Part:
    pads = []
    for name, num in PIN.items():
        lx, ly, w, h = qfn_local(num)
        pads.append(Pad(str(num), lx, ly, w, h, nets.get(name, "")))
    return Part(ref, "ATtiny1616", "qfn", x, y, pads)


def _grove(x, y) -> Part:
    # Ursprung = Mitte der Signalkontakte. Öffnung in -x (trockene Kante), wie HW4-SMD-2.0-90D auf der Seeed-Platine.
    spec = [
        ("1", 0.0, -3.0, 2.74, 1.01, "SCL"),
        ("2", 0.0, -1.0, 2.74, 1.01, "SDA"),
        ("3", 0.0, 1.0, 2.74, 1.01, "VCC"),
        ("4", 0.0, 3.0, 2.74, 1.01, "GND"),
        ("SS1", -7.4, -5.4, 3.0, 1.5, "GND"),
        ("SS2", -7.4, 5.4, 3.0, 1.5, "GND"),
    ]
    return Part("J1", "Grove", "grove", x, y, [Pad(*s[:5], s[5]) for s in spec])


def _mount_hole(ref: str, x: float) -> Part:
    return Part(ref, "M2.5", "mount", x, MOUNT_Y, [
        Pad("", 0.0, 0.0, MOUNT_PAD, MOUNT_PAD, "", paste=False, mask=True),
    ])


def _hdr() -> Part:
    """Vier Löcher, Raster 2,54 mm. Pin 1 GND, 2 VCC, 3 UPDI von U1, 4 UPDI von U2."""
    pitch = 2.54
    spec = [("1", "GND"), ("2", "VCC"), ("3", "UPDI_U1"), ("4", "UPDI_U2")]
    return Part("J3", "UPDI", "hdr", HDR_X, HDR_Y, [
        Pad(name, 0.0, i * pitch, 1.6, 1.6, net, paste=False)
        for i, (name, net) in enumerate(spec)
    ])


def _electrode(i: int) -> Part:
    net = f"E{i + 1:02d}"
    h = ELEC_Y1 - ELEC_Y0
    return Part(f"E{i + 1}", net, "electrode", elec_x(i), (ELEC_Y0 + ELEC_Y1) / 2, [
        Pad("1", 0.0, 0.0, ELEC_ALONG, h, net, mask=False, paste=False),
    ])


def _mcu_nets(which: str) -> dict:
    nets = {
        "GND": "GND", "EP": "GND", "VDD": "VCC",
        "PA0": "UPDI_U1" if which == "U1" else "UPDI_U2",
        "PA1": "SDA", "PA2": "SCL",
        "PA3": "GND" if which == "U1" else "VCC",
    }
    for elec, mcu, pin, _ref in SENSORS:
        if mcu == which:
            nets[pin] = f"{which}_{pin}"
    return nets


def build_parts() -> list[Part]:
    u1x, u1y = U1_POS
    u2x, u2y = U2_POS
    h = HEAD
    parts = [
        _hdr(),
        _grove(*CONN),
        _qfn("U1", u1x, u1y, _mcu_nets("U1")),
        _qfn("U2", u2x, u2y, _mcu_nets("U2")),
        # I2C-Pullups, einmal für den Bus. PA1/PA2 liegen direkt auf SDA/SCL.
        _r("R1", "4.7k", 15.6 + h, 4.6, "SCL", "VCC"),
        _r("R2", "4.7k", 15.6 + h, 6.6, "SDA", "VCC"),
        # Abblockung am Rand, unter der ersten Sense-Bahn. Nicht neben U1: dort fällt PA4.
        _c("C1", "100nF", 28.3 + h, 1.05, "GND", "VCC"),
        _c("C2", "4.7uF", 32.5 + h, 1.05, "GND", "VCC"),
        # Neben dem U2-Bus, nicht zwischen den Chips: dort ist die Flucht von U1 Pin 11–15.
        _c("C3", "100nF", 16.8 + h, 9.35, "GND", "VCC"),
        _c("C4", "4.7uF", 19.4 + h, 9.35, "GND", "VCC"),
    ]
    for elec, mcu, pin, ref in SENSORS:
        i = elec - 1
        parts.append(_r(ref, "1k", RES_X_EVEN if i % 2 == 0 else RES_X_ODD, lane_y(i),
                        f"{mcu}_{pin}", f"E{elec:02d}"))
    for i in range(N):
        parts.append(_electrode(i))
    parts.append(_mount_hole("MH1", MOUNT_X))
    return parts


PARTS = build_parts()


def elec_nets() -> set[str]:
    return {f"E{i:02d}" for i in range(1, N + 1)}
